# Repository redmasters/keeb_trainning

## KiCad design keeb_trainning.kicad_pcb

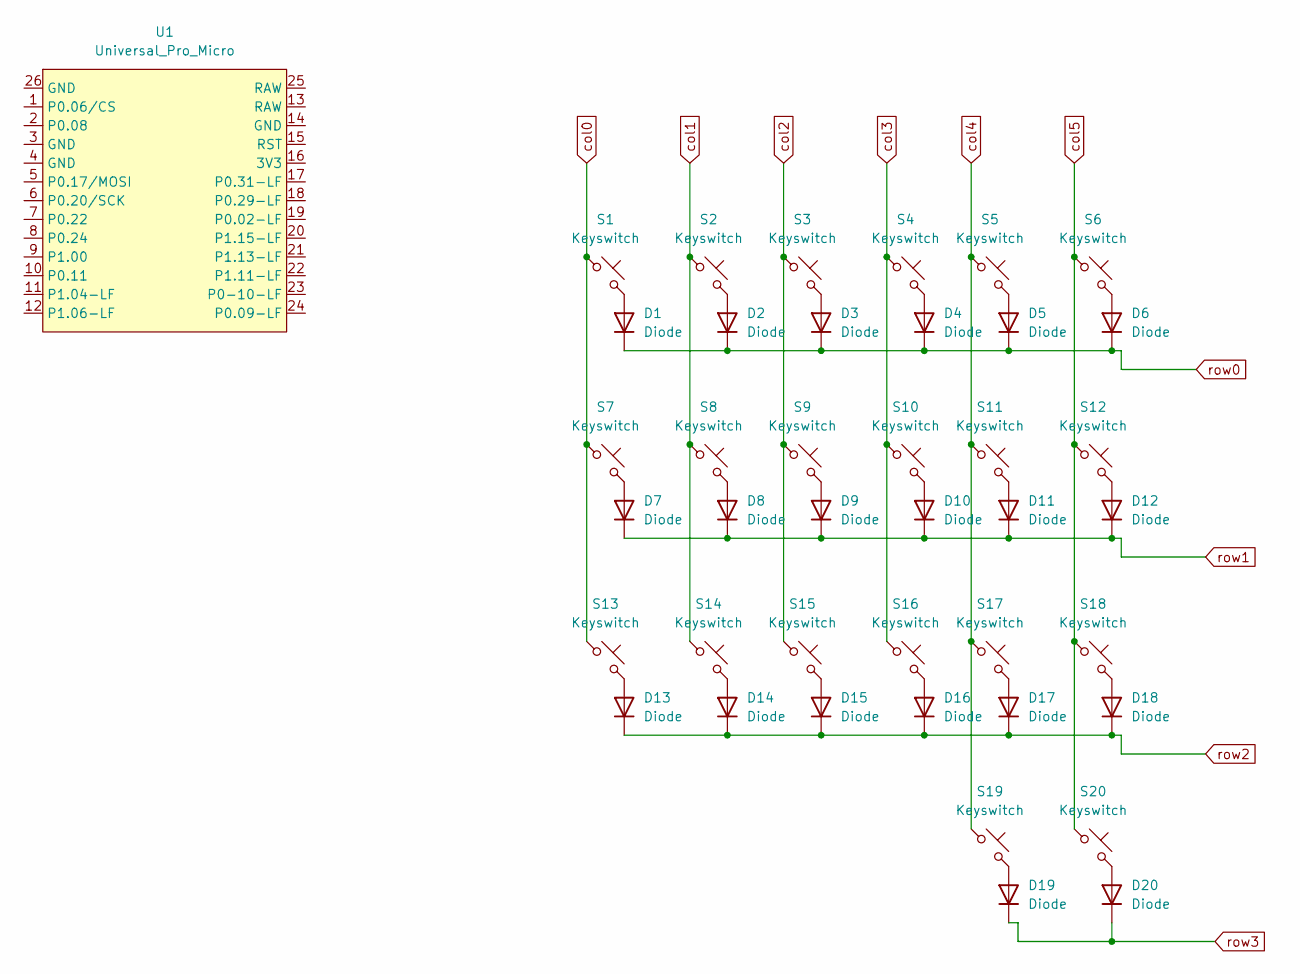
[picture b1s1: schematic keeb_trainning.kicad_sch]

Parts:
D1, D2, D3, D4, D5, D6, D7, D8, D9, D10, D11, D12, D13, D14, D15, D16, D17, D18, D19, D20: Diode; Diode_SOD-123
S1, S2, S3, S4, S5, S6, S7, S8, S9, S10, S11, S12, S13, S14, S15, S16, S17, S18, S19, S20: Keyswitch; Hotswap_Choc_V1
U1: Universal_Pro_Micro; Universal_Pro_Micro_Footprint

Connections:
unnamed: D1.2 (A), S1.2
unnamed: D2.2 (A), S2.2
unnamed: D3.2 (A), S3.2
unnamed: D4.2 (A), S4.2
unnamed: D5.2 (A), S5.2
unnamed: D6.2 (A), S6.2
unnamed: D7.2 (A), S7.2
unnamed: D8.2 (A), S8.2
unnamed: D9.2 (A), S9.2
unnamed: D10.2 (A), S10.2
unnamed: D11.2 (A), S11.2
unnamed: D12.2 (A), S12.2
unnamed: D13.2 (A), S13.2
unnamed: D14.2 (A), S14.2
unnamed: D15.2 (A), S15.2
unnamed: D16.2 (A), S16.2
unnamed: D17.2 (A), S17.2
unnamed: D18.2 (A), S18.2
unnamed: D19.2 (A), S19.2
unnamed: D20.2 (A), S20.2
col0: S1.1, S7.1, S13.1
col1: S2.1, S8.1, S14.1
col2: S3.1, S9.1, S15.1
col3: S4.1, S10.1, S16.1
col4: S5.1, S11.1, S17.1, S19.1
col5: S6.1, S12.1, S18.1, S20.1
row0: D1.1 (K), D2.1 (K), D3.1 (K), D4.1 (K), D5.1 (K), D6.1 (K)
row1: D7.1 (K), D8.1 (K), D9.1 (K), D10.1 (K), D11.1 (K), D12.1 (K)
row2: D13.1 (K), D14.1 (K), D15.1 (K), D16.1 (K), D17.1 (K), D18.1 (K)
row3: D19.1 (K), D20.1 (K)

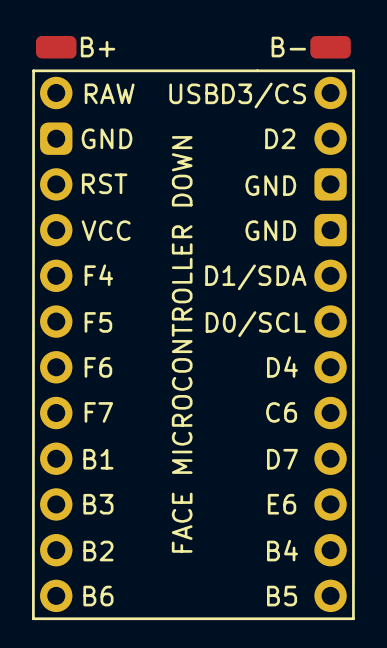
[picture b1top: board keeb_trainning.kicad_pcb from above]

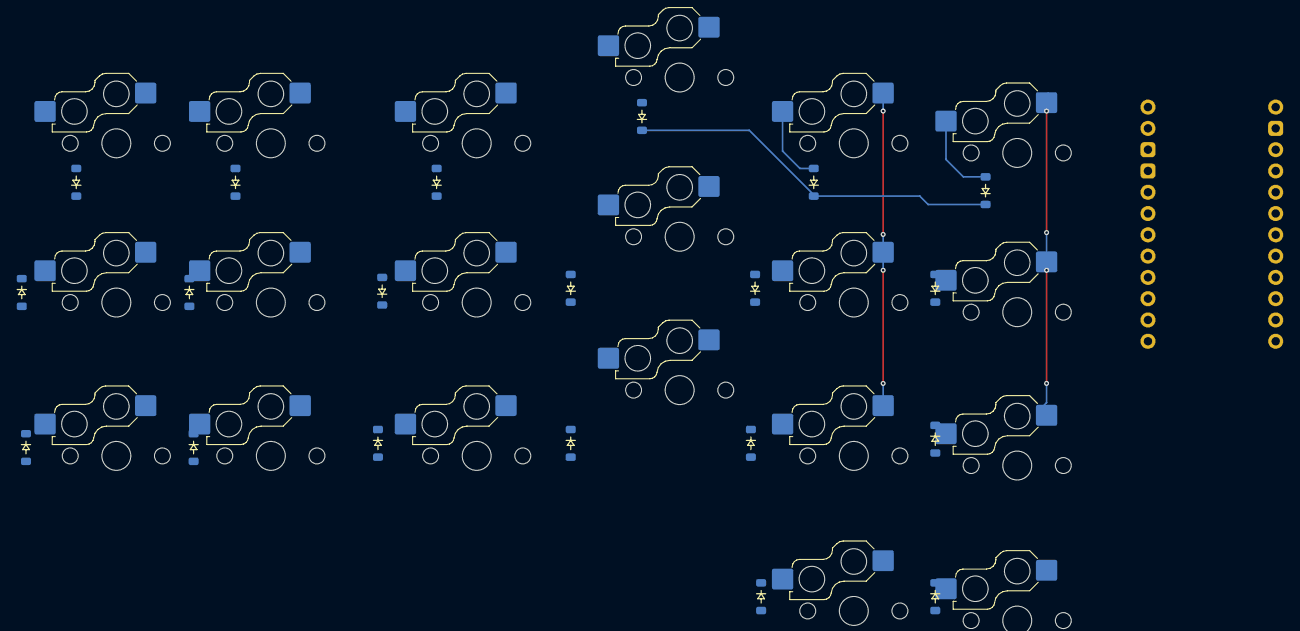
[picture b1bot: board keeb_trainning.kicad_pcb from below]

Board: 2 copper layers, 41 parts (20 on the bottom side), 30 nets.

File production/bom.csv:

Designator,Footprint,Quantity,Value,LCSC Part #
"D1, D10, D11, D12, D13, D14, D15, D16, D17, D18, D19, D2, D20, D3, D4, D5, D6, D7, D8, D9",Diode_SOD-123,20,Diode,
"S1, S10, S11, S12, S13, S14, S15, S16, S17, S18, S2, S3, S4, S5, S6, S7, S8, S9",Choc_V2,18,Keyswitch,
"S19, S20",Choc_V2_1.50u_90deg,2,Keyswitch,
U1,Arduino_Pro_Micro,1,Arduino_Pro_Micro,

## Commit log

2024-06-03 :tada: FEAT: First commit
2024-06-03 :books: DOC: Adicionado README
2024-06-03 :sparkles: FEAT: First PCB!
2024-06-03 :sparkles: FEAT: Adicionado assets
2024-06-03 Rename pcb (1).png to pcb1.png
2024-06-03 Rename pcb (2).png to pcb2.png
2024-06-03 :recycle: REFACT: Corrigido nome da pasta
2024-06-03 :construction: WIP: Drawing schematics
2024-06-05 :construction: WIP: Redraw wires
2024-06-05 :books: DOC: Added 'current.png' to assets
2024-06-05 :books: DOC:(Readme) updated
2024-06-06 :construction: WIP: Added hotswap
